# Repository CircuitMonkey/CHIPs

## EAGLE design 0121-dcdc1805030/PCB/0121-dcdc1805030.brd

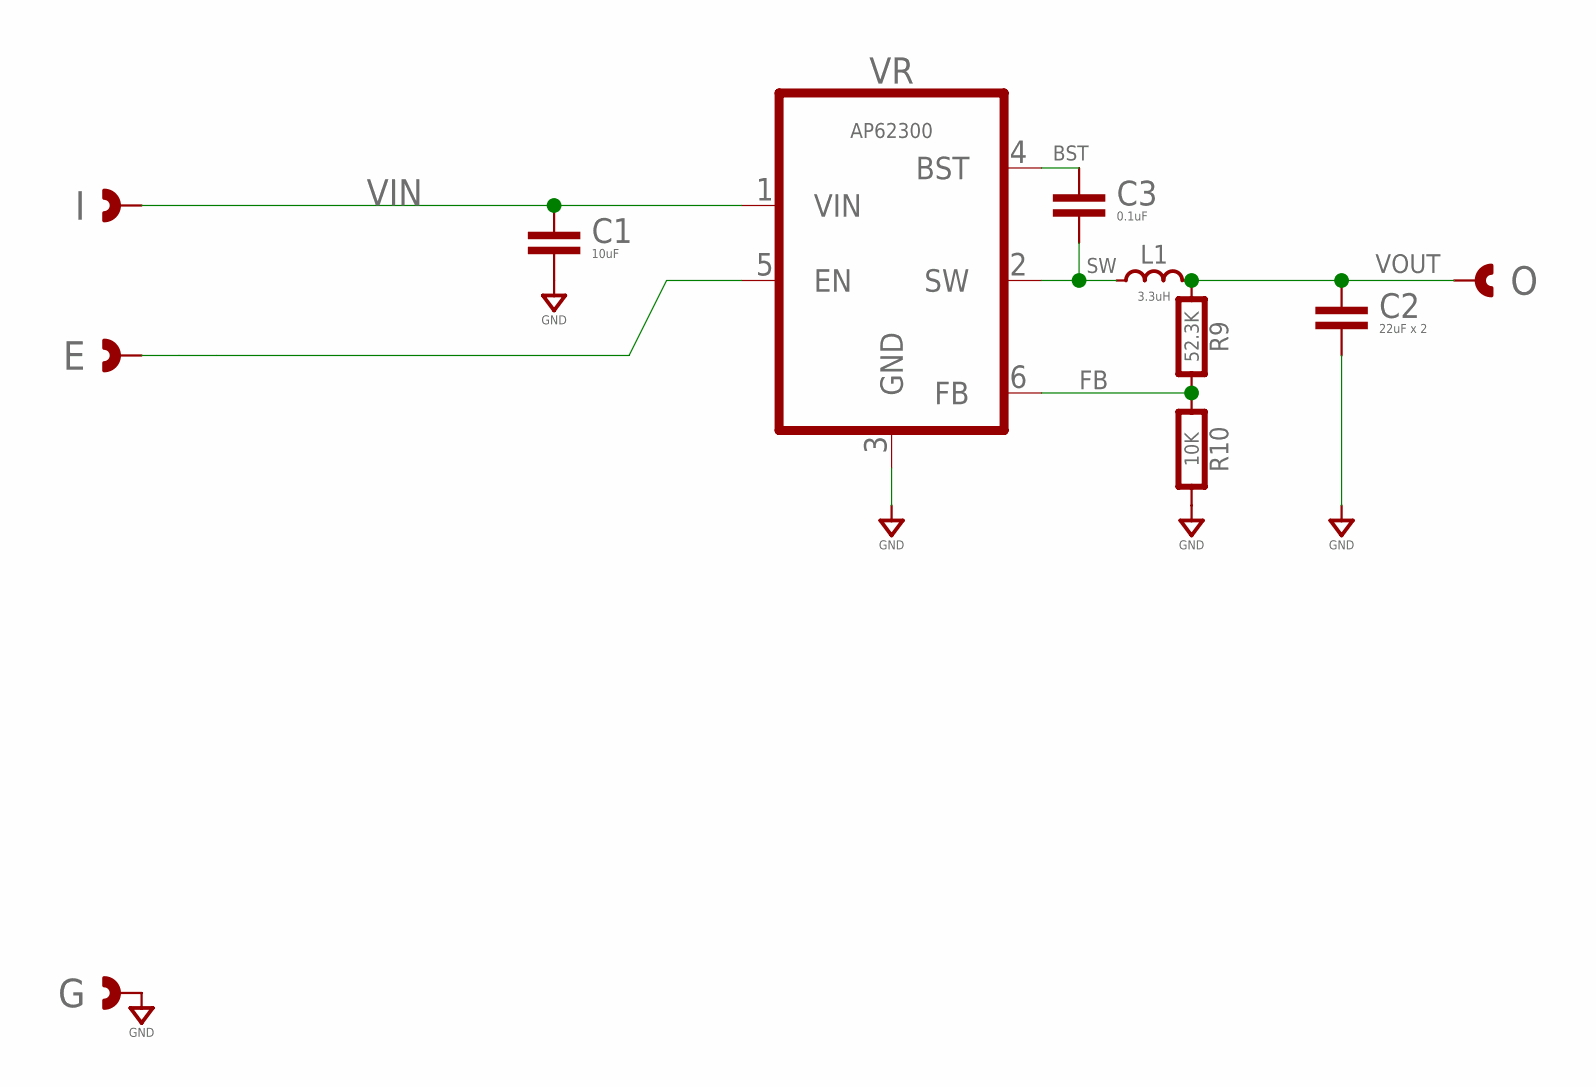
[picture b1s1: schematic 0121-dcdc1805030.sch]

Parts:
C1: 10uF; 0603-CAP
C2: 22uF x 2; 0603-CAP
C3: 0.1uF; 0603-CAP
E: CAST-01X12.00MM; CAST01-2.00MM
G: CAST-01X12.00MM; CAST01-2.00MM
I: CAST-01X12.00MM; CAST01-2.00MM
L1: 3.3uH; IND-SRN5040; MPN SRN5040-3R3M
O: CAST-01X12.00MM; CAST01-2.00MM
R9: 52.3K; 0603-RES
R10: 10K; 0603-RES
VR: AP62300; SOT-563-6

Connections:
BST: C3.1, VR.4 (BST)
FB: R9.2, R10.1, VR.6 (FB)
GND: C1.2, C2.2, G.1, G.P$1, G.P$2, R10.2, VR.3 (GND)
unnamed: E.1, E.P$1, E.P$2, VR.5 (EN)
SW: C3.2, L1.2, VR.2 (SW)
VIN: C1.1, I.1, I.P$1, I.P$2, VR.1 (VIN)
VOUT: C2.1, L1.1, O.1, O.P$1, O.P$2, R9.1

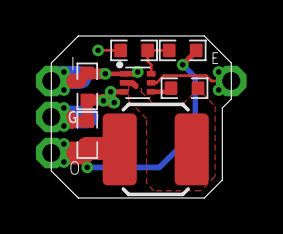
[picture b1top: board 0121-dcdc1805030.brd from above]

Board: 2 copper layers, 10.0 x 9.0 mm, 11 parts (0 on the bottom side), 7 nets.

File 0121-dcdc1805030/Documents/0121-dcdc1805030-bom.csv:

"Part";"Value";"Device";"Package";"Description";"COST01";"MFR";"MPN";"VALUE";
"C1";"10uF";"CAPACITOR0603";"0603-CAP";"Capacitor";"";"";"";"";
"C2";"22uF x 2";"CAPACITOR0603";"0603-CAP";"Capacitor";"";"";"";"";
"C3";"0.1uF";"CAPACITOR0603";"0603-CAP";"Capacitor";"";"";"";"";
"E";"CAST-01X12.00MM";"CAST-01X12.00MM";"CAST01-2.00MM";"Castelated Edge Hole Pad";"";"";"";"";
"G";"CAST-01X12.00MM";"CAST-01X12.00MM";"CAST01-2.00MM";"Castelated Edge Hole Pad";"";"";"";"";
"I";"CAST-01X12.00MM";"CAST-01X12.00MM";"CAST01-2.00MM";"Castelated Edge Hole Pad";"";"";"";"";
"L1";"3.3uH";"INDUCTORSMD-05X04MM";"IND-SRN5040";"Inductor";"";"Bourns";"SRN5040-3R3M";"";
"O";"CAST-01X12.00MM";"CAST-01X12.00MM";"CAST01-2.00MM";"Castelated Edge Hole Pad";"";"";"";"";
"R9";"52.3K";"RESISTOR0603";"0603-RES";"Resistor";"";"";"";"";
"R10";"10K";"RESISTOR0603";"0603-RES";"Resistor";"";"";"";"";
"VR";"AP62300";"BUCKAP62300";"SOT-563-6";"Buck Regulator";"0.50";"Diodes, Inc.";"AP62301Z6-7";"AP62300";

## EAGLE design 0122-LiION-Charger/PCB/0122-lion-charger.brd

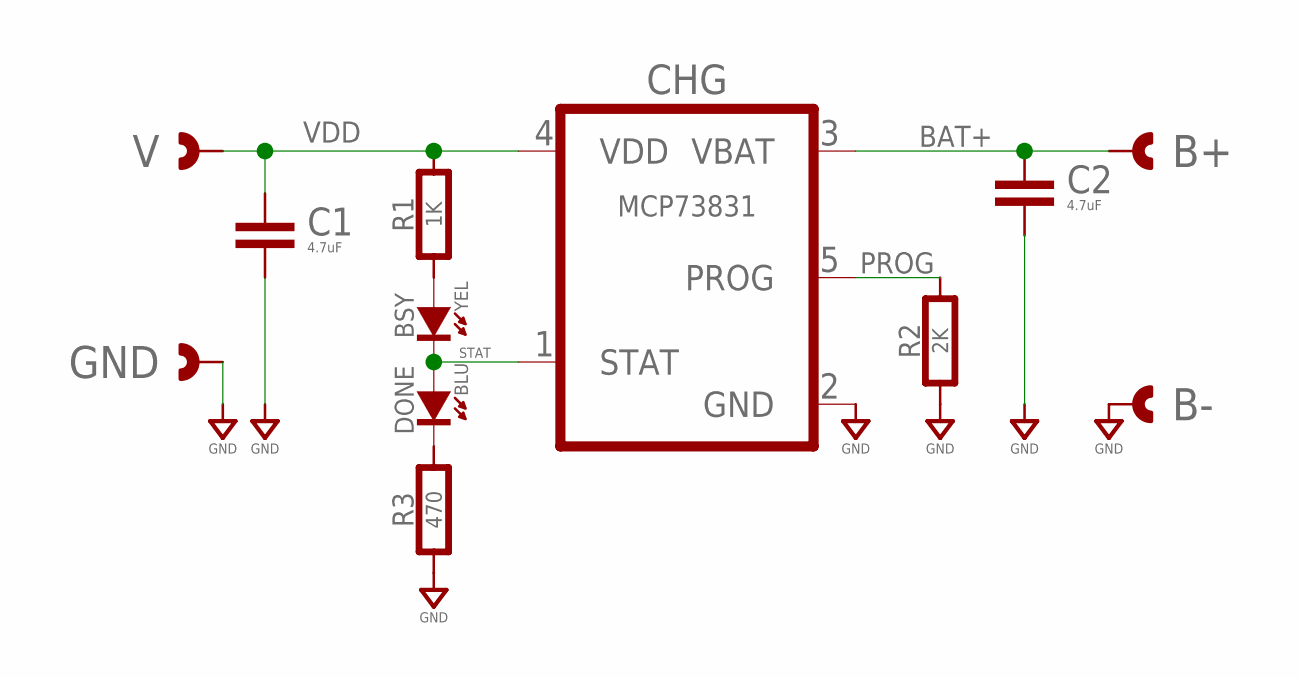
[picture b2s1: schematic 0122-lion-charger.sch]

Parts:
B+: CAST-01X12.00MM; CAST01-2.00MM
B-: CAST-01X12.00MM; CAST01-2.00MM
BSY: YEL; SMD_0603
C1, C2: 4.7uF; 0603-CAP
CHG: MCP73831; SOT-23-5
DONE: BLU; SMD_0603
GND: CAST-01X12.00MM; CAST01-2.00MM
R1: 1K; 0603-RES
R2: 2K; 0603-RES
R3: 470; 0603-RES
V: CAST-01X12.00MM; CAST01-2.00MM

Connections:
BAT+: B+.1, B+.P$1, B+.P$2, C2.1, CHG.3 (VBAT)
GND: B-.1, B-.P$1, B-.P$2, C1.2, C2.2, CHG.2 (GND), GND.1, GND.P$1, GND.P$2, R2.1, R3.1
unnamed: BSY.A, R1.1
unnamed: DONE.K (C), R3.2
PROG: CHG.5 (PROG), R2.2
STAT: BSY.K (C), CHG.1 (STAT), DONE.A
VDD: C1.1, CHG.4 (VDD), R1.2, V.1, V.P$1, V.P$2

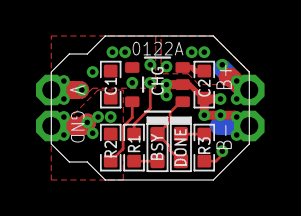
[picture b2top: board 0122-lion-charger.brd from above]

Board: 2 copper layers, 11.0 x 8.0 mm, 12 parts (0 on the bottom side), 7 nets.

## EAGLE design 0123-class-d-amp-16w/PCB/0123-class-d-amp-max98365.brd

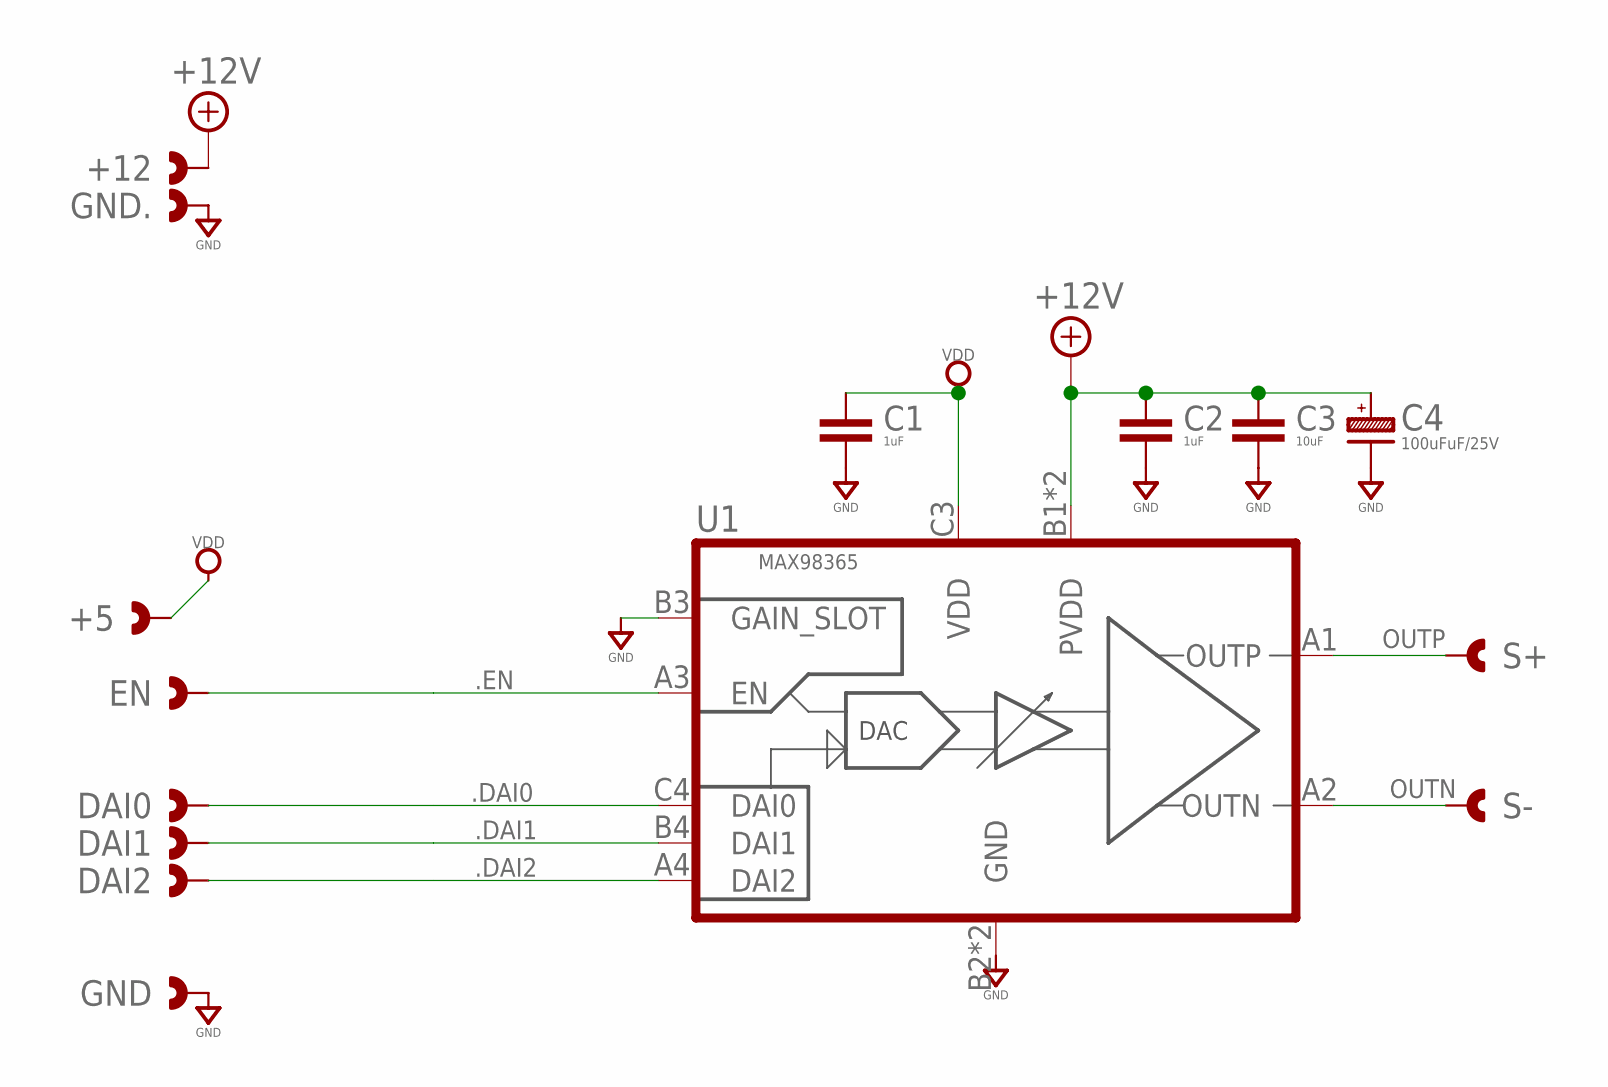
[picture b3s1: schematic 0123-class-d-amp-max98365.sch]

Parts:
+5, +12: CAST-01X12.00MM; CAST01-2.00MM
C1, C2: 1uF; 0603-CAP
C3: 10uF; 0603-CAP
C4: 100uFuF/25V; CAP_ALUM_SMT_6.3
DAI0, DAI1, DAI2: CAST-01X12.00MM; CAST01-2.00MM
EN: CAST-01X12.00MM; CAST01-2.00MM
GND, GND.: CAST-01X12.00MM; CAST01-2.00MM
S+: CAST-01X12.00MM; CAST01-2.00MM
S-: CAST-01X12.00MM; CAST01-2.00MM
U1: MAX98365; 12WLP

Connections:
+12V: +12.1, +12.P$1, +12.P$2, C2.1, C3.1, C4.+, U1.B1 (PVDD), U1.C1 (PVDD)
.DAI0: DAI0.1, DAI0.P$1, DAI0.P$2, U1.C4 (DAI0)
.DAI1: DAI1.1, DAI1.P$1, DAI1.P$2, U1.B4 (DAI1)
.DAI2: DAI2.1, DAI2.P$1, DAI2.P$2, U1.A4 (DAI2)
.EN: EN.1, EN.P$1, EN.P$2, U1.A3 (EN)
GND: C1.2, C2.2, C3.2, C4.- (N), GND.1, GND.P$1, GND.P$2, GND..1, GND..P$1, GND..P$2, U1.B2 (GND), U1.B3 (GAIN_SLOT), U1.C2 (GND)
OUTN: S-.1, S-.P$1, S-.P$2, U1.A2 (OUTN)
OUTP: S+.1, S+.P$1, S+.P$2, U1.A1 (OUTP)
VDD: +5.1, +5.P$1, +5.P$2, C1.1, U1.C3 (VDD)

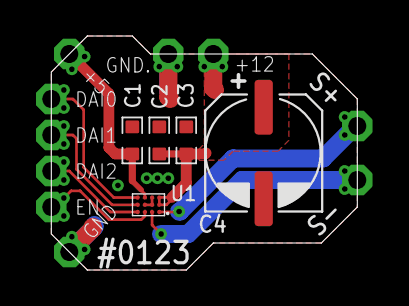
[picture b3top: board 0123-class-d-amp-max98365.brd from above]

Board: 2 copper layers, 17.0 x 13.0 mm, 15 parts (0 on the bottom side), 9 nets.

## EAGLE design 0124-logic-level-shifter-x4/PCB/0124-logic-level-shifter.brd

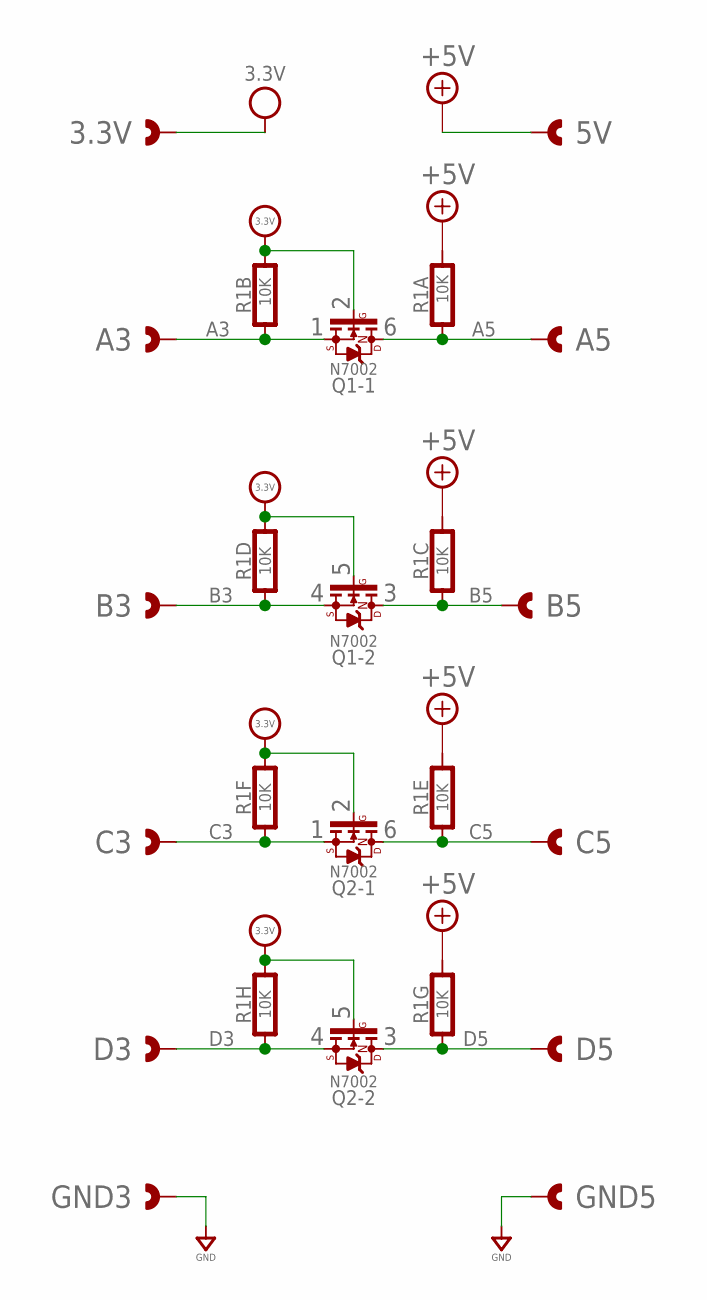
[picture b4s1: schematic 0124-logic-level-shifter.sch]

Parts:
3.3V, 5V: CAST-01X12.00MM; CAST01-2.00MM
A3, A5: CAST-01X12.00MM; CAST01-2.00MM
B3, B5: CAST-01X12.00MM; CAST01-2.00MM
C3, C5: CAST-01X12.00MM; CAST01-2.00MM
D3, D5: CAST-01X12.00MM; CAST01-2.00MM
GND3, GND5: CAST-01X12.00MM; CAST01-2.00MM
Q1, Q2: N7002; SOT-563
R1: 10K; RESNET_0402_X8

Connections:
+3.3V: 3.3V.1, 3.3V.P$1, 3.3V.P$2, Q1.2 (G), Q1.5 (G), Q2.2 (G), Q2.5 (G), R1.9 (2), R1.11 (2), R1.13 (2), R1.15 (2)
+5V: 5V.1, 5V.P$1, 5V.P$2, R1.10 (2), R1.12 (2), R1.14 (2), R1.16 (2)
A3: A3.1, A3.P$1, A3.P$2, Q1.1 (S), R1.2 (1)
A5: A5.1, A5.P$1, A5.P$2, Q1.6 (D), R1.1
B3: B3.1, B3.P$1, B3.P$2, Q1.4 (S), R1.4 (1)
B5: B5.1, B5.P$1, B5.P$2, Q1.3 (D), R1.3 (1)
C3: C3.1, C3.P$1, C3.P$2, Q2.1 (S), R1.6 (1)
C5: C5.1, C5.P$1, C5.P$2, Q2.6 (D), R1.5 (1)
D3: D3.1, D3.P$1, D3.P$2, Q2.4 (S), R1.8 (1)
D5: D5.1, D5.P$1, D5.P$2, Q2.3 (D), R1.7 (1)
GND: GND3.1, GND3.P$1, GND3.P$2, GND5.1, GND5.P$1, GND5.P$2

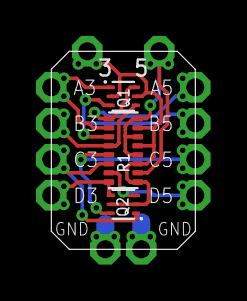
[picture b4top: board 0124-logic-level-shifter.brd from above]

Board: 2 copper layers, 8.0 x 11.0 mm, 15 parts (0 on the bottom side), 11 nets.

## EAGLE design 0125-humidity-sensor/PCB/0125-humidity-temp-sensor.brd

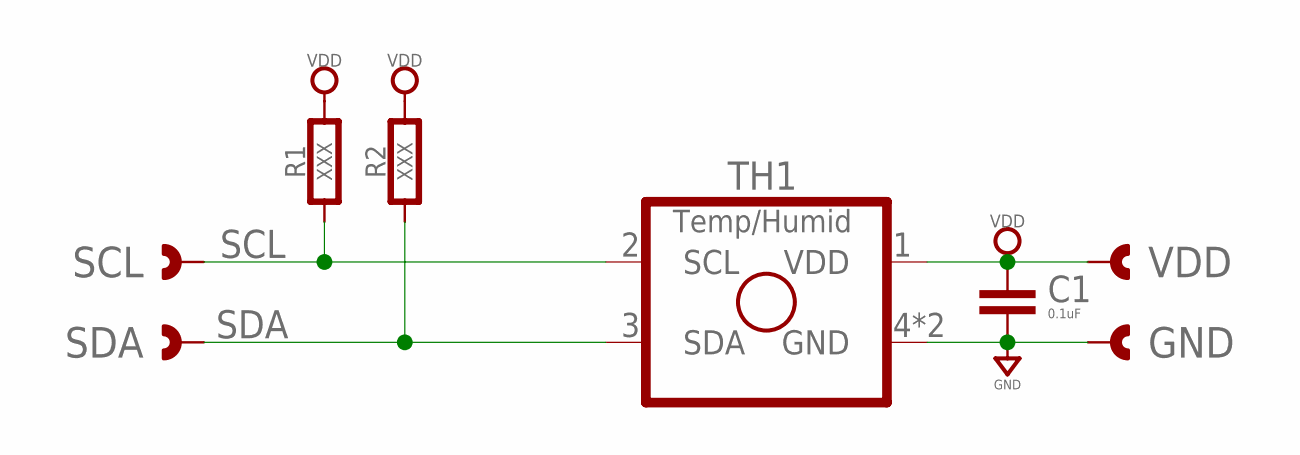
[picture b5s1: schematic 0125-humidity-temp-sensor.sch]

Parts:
C1: 0.1uF; 0402-CAP
GND: CAST-01X12.00MM; CAST01-2.00MM
R1, R2: XXX; 0402-RES
SCL: CAST-01X12.00MM; CAST01-2.00MM
SDA: CAST-01X12.00MM; CAST01-2.00MM
TH1: Temp/Humid; SHTC3
VDD: CAST-01X12.00MM; CAST01-2.00MM

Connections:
GND: C1.2, GND.1, GND.P$1, GND.P$2, TH1.4 (GND), TH1.PAD (GND)
SCL: R1.1, SCL.1, SCL.P$1, SCL.P$2, TH1.2 (SCL)
SDA: R2.1, SDA.1, SDA.P$1, SDA.P$2, TH1.3 (SDA)
VDD: C1.1, R1.2, R2.2, TH1.1 (VDD), VDD.1, VDD.P$1, VDD.P$2

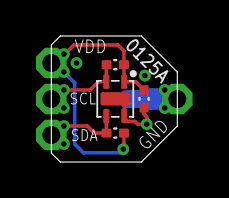
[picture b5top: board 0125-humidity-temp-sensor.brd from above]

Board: 2 copper layers, 7.0 x 7.0 mm, 8 parts (0 on the bottom side), 4 nets.

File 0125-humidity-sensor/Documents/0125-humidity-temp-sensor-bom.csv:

"Part";"Value";"Device";"Package";"Description";"COST01";"COST100";"MFR";"MPN";"VALUE";
"C1";"0.1uF";"CAPACITOR0402";"0402-CAP";"Capacitor";"";"";"";"";"";
"GND";"CAST-01X12.00MM";"CAST-01X12.00MM";"CAST01-2.00MM";"Castelated Edge Hole Pad";"";"";"";"";"";
"R1";"4.7K";"RESISTOR0402";"0402-RES";"Resistor";"";"";"";"";"";
"R2";"4.7K";"RESISTOR0402";"0402-RES";"Resistor";"";"";"";"";"";
"SCL";"CAST-01X12.00MM";"CAST-01X12.00MM";"CAST01-2.00MM";"Castelated Edge Hole Pad";"";"";"";"";"";
"SDA";"CAST-01X12.00MM";"CAST-01X12.00MM";"CAST01-2.00MM";"Castelated Edge Hole Pad";"";"";"";"";"";
"TH1";"Temp/Humid";"I2C-SHTC3";"SHTC3";"I2C Type Sensor";"2.50";"1.50";"Sensiron";"SHTC3";"Temp/Humid";
"VDD";"CAST-01X12.00MM";"CAST-01X12.00MM";"CAST01-2.00MM";"Castelated Edge Hole Pad";"";"";"";"";"";

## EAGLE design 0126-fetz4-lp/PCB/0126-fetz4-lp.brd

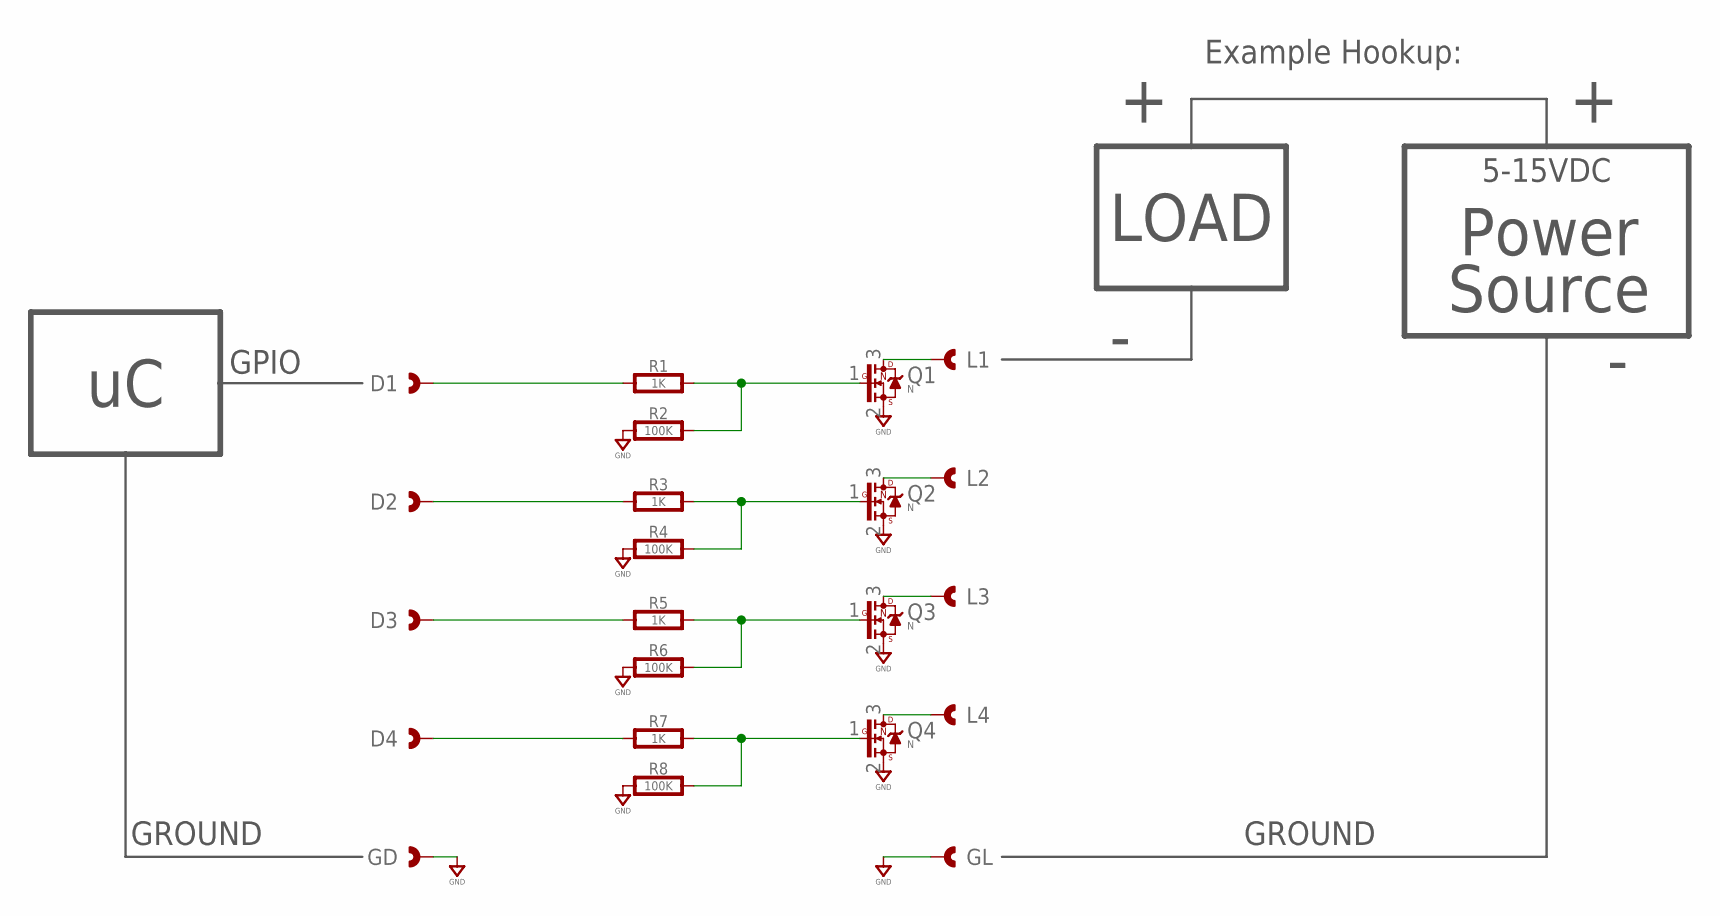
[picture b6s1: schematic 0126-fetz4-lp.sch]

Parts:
D1, D2, D3, D4: CAST-01X12.00MM; CAST01-2.00MM
GD: CAST-01X12.00MM; CAST01-2.00MM
GL: CAST-01X12.00MM; CAST01-2.00MM
L1, L2, L3, L4: CAST-01X12.00MM; CAST01-2.00MM
Q1, Q2, Q3, Q4: N; SOT-23
R1, R3, R5, R7: 1K; 0603-RES
R2, R4, R6, R8: 100K; 0603-RES

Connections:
GND: GD.1, GD.P$1, GD.P$2, GL.1, GL.P$1, GL.P$2, Q1.2 (S), Q2.2 (S), Q3.2 (S), Q4.2 (S), R2.1, R4.1, R6.1, R8.1
unnamed: L1.1, L1.P$1, L1.P$2, Q1.3 (D)
unnamed: D1.1, D1.P$1, D1.P$2, R1.1
unnamed: Q1.1 (G), R1.2, R2.2
unnamed: L2.1, L2.P$1, L2.P$2, Q2.3 (D)
unnamed: D2.1, D2.P$1, D2.P$2, R3.1
unnamed: Q2.1 (G), R3.2, R4.2
unnamed: L3.1, L3.P$1, L3.P$2, Q3.3 (D)
unnamed: D3.1, D3.P$1, D3.P$2, R5.1
unnamed: Q3.1 (G), R5.2, R6.2
unnamed: L4.1, L4.P$1, L4.P$2, Q4.3 (D)
unnamed: D4.1, D4.P$1, D4.P$2, R7.1
unnamed: Q4.1 (G), R7.2, R8.2

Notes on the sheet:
LOAD
Power Source
Example Hookup:
5-15VDC
GROUND
GPIO

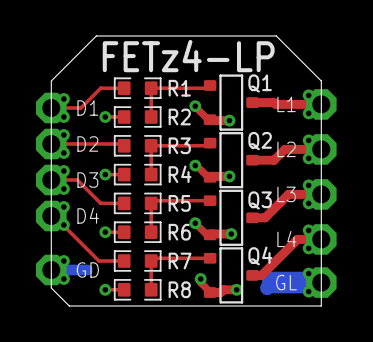
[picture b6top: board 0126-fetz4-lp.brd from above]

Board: 2 copper layers, 15.0 x 15.0 mm, 22 parts (0 on the bottom side), 13 nets.

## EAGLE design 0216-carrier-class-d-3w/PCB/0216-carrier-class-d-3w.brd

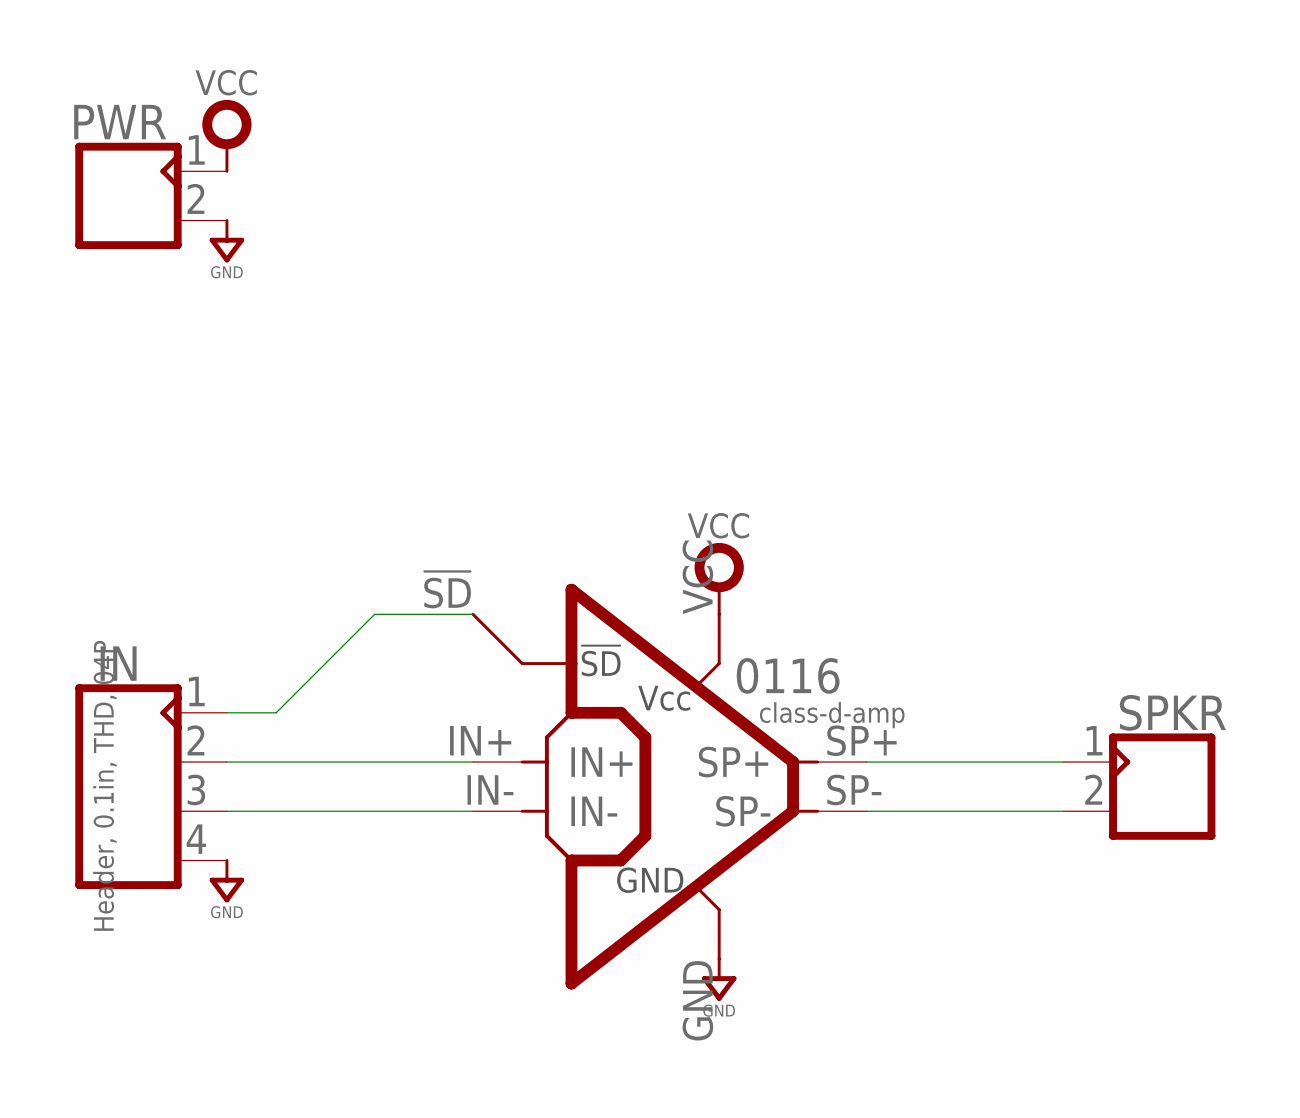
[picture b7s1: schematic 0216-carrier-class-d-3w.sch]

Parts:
0116: class-d-amp; 0116A
IN: Header, 0.1in, THD, 04P; MA04X1-VT-THD
PWR: CON_02X1-2.54MM-THD-VT; MA02X1-VT-THD
SPKR: CON_02X1-2.54MM-THD-VT; MA02X1-VT-THD

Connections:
GND: 0116.GND, IN.4, PWR.2
unnamed: 0116.IN-, IN.3
unnamed: 0116.IN+, IN.2
unnamed: 0116.!SD, IN.1
unnamed: 0116.SP-, SPKR.2
unnamed: 0116.SP+, SPKR.1
VCC: 0116.VCC, PWR.1

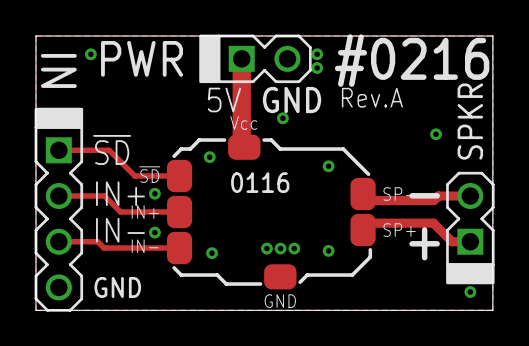
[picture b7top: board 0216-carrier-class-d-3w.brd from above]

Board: 2 copper layers, 25.4 x 15.2 mm, 4 parts (0 on the bottom side), 7 nets.

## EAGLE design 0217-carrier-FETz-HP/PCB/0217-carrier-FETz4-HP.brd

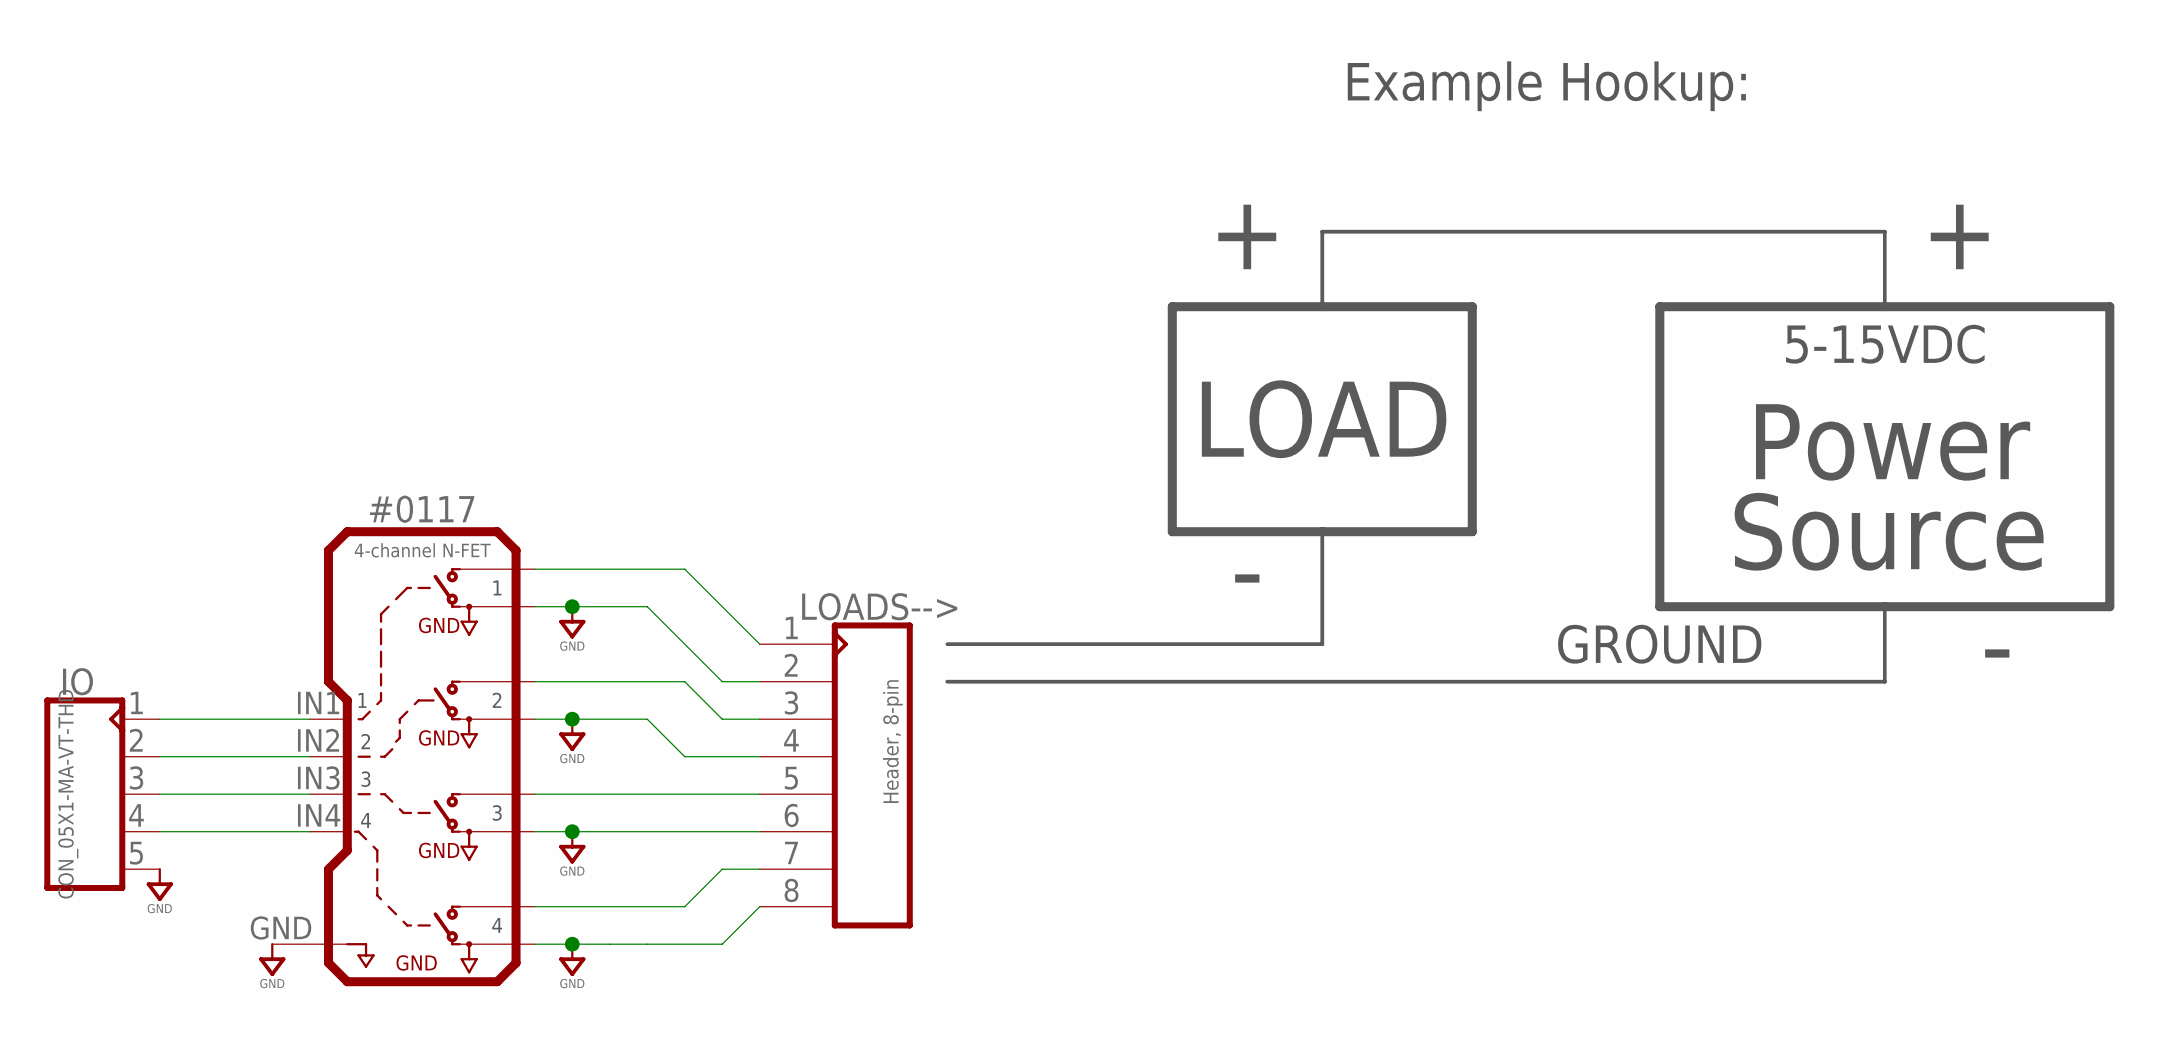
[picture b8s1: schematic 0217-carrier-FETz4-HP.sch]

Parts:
#0117: 4-channel N-FET; 0117A
IO: CON_05X1-MA-VT-THD; MA05X1-VT-THD
LOADS-->: Header, 8-pin; MA08X1-VT-THD

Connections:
GND: #0117.GND, #0117.GND1, #0117.GND2, #0117.GND3, #0117.GND4, IO.5, LOADS-->.2, LOADS-->.4, LOADS-->.6, LOADS-->.8
unnamed: #0117.IN4 (4), IO.4
unnamed: #0117.IN3 (3), IO.3
unnamed: #0117.IN2 (2), IO.2
unnamed: #0117.IN1 (1), IO.1
unnamed: #0117.OUT1 (V1), LOADS-->.1
unnamed: #0117.OUT2 (V2), LOADS-->.3
unnamed: #0117.OUT3 (V3), LOADS-->.5
unnamed: #0117.OUT4 (V4), LOADS-->.7

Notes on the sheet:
LOAD
Power Source
Example Hookup:
5-15VDC
GROUND

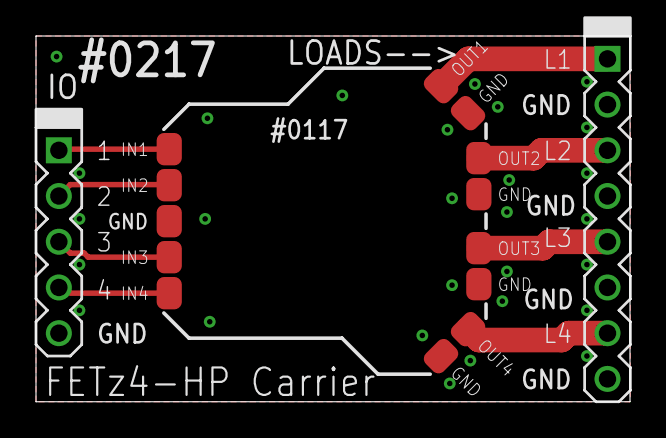
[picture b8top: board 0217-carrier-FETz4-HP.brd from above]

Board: 2 copper layers, 33.0 x 20.3 mm, 3 parts (0 on the bottom side), 9 nets.
